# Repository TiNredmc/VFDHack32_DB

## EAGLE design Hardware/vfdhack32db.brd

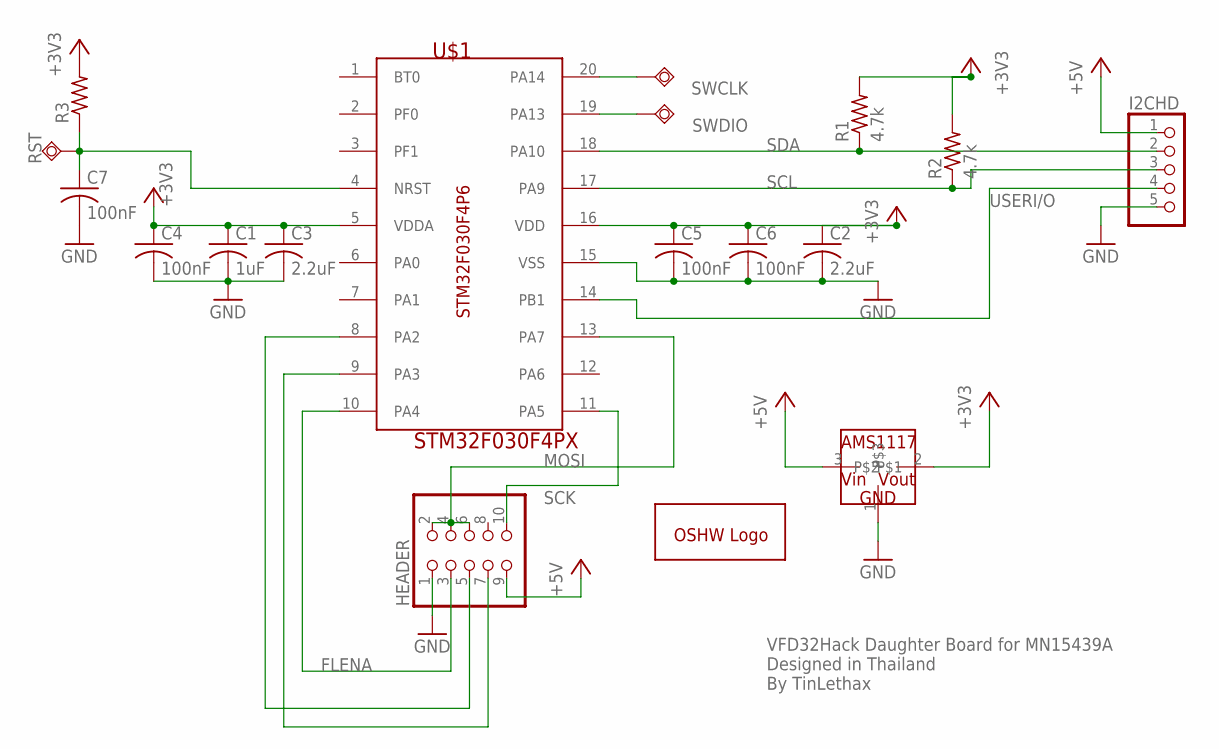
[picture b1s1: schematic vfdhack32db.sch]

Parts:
C1: 1uF; C0603
C2, C3: 2.2uF; C0603
C4, C5, C6, C7: 100nF; C1206K
GOLD_ORB_SM1: OSHWLOGOLOGO5MM; OSHW_5MM
HEADER: PINHD-2X5; 2X05
I2CHD: PINHD-1X5; 1X05
R1, R2: 4.7k; R0603
R3: R-US_R0603; R0603
RST: TPSQTP10SQ; TP10SQ
SWCLK: TPSQTP10SQ; TP10SQ
SWDIO: TPSQTP10SQ; TP10SQ
U$1: STM32F030F4PX; SOP65P640X120-20N
U$2: AMS1117; SOT223

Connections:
+3V3: C1.1, C2.1, C3.1, C4.1, C5.1, C6.1, R1.2, R2.2, R3.2, U$1.5 (VDDA), U$1.16 (VDD), U$2.2
+5V: HEADER.9, I2CHD.1, U$2.3
FLENA: HEADER.3, U$1.10 (PA4)
GND: C1.2, C2.2, C3.2, C4.2, C5.2, C6.2, C7.2, HEADER.1, I2CHD.5, U$1.15 (VSS), U$2.1
MOSI: HEADER.2, HEADER.4, HEADER.6, U$1.13 (PA7)
unnamed: C7.1, R3.1, RST.TP, U$1.4 (NRST)
unnamed: SWCLK.TP, U$1.20 (PA14)
unnamed: SWDIO.TP, U$1.19 (PA13)
unnamed: HEADER.5, U$1.8 (PA2)
unnamed: HEADER.7, U$1.9 (PA3)
SCK: HEADER.10, U$1.11 (PA5)
SCL: I2CHD.3, R2.1, U$1.17 (PA9)
SDA: I2CHD.2, R1.1, U$1.18 (PA10)
USERI/O: I2CHD.4, U$1.14 (PB1)

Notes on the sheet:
VFD32Hack Daughter Board for MN15439A Designed in Thailand By TinLethax

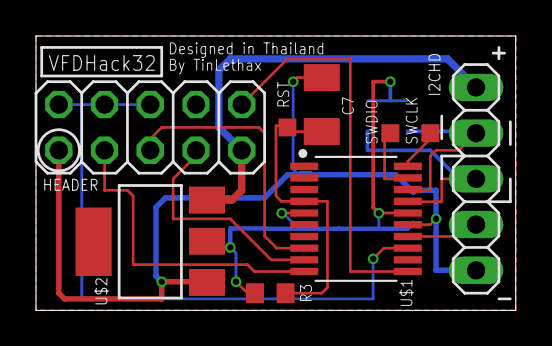
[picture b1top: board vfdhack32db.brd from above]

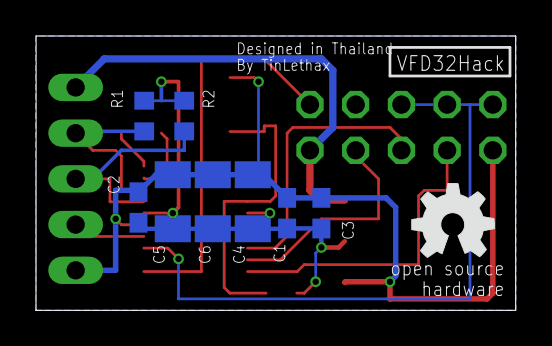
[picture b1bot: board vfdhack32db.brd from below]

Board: 2 copper layers, 26.6 x 15.2 mm, 18 parts (9 on the bottom side), 14 nets.

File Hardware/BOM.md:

# Bill of materials
1. x1 AMS1117 3v3   
2. x4 100nF 1206 capacitor 16v  
3. x2 2.2uF 0603 capacitor 16v   
4. x1 1uF 	0603 capacitor 16v  
5. x1 1x5 Male Pin header  
6. x1 2x5 Female Pin header or x2 1x5 Female Pin header 
7. x2 4.7k 0603  resistor
8. [OPTIONAL] x1 10k 0603 resistor for NRST pull up (internal pull up is there)  
9. x1 STM32F030F4P6 (TSSOP 20).

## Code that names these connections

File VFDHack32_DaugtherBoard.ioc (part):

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Mcu.Name=STM32F030F4Px
Mcu.Package=TSSOP20
Mcu.UserName=STM32F030F4Px
PA10.Mode=I2C
PA10.Signal=I2C1_SDA
PA13.Mode=Serial_Wire
PA13.Signal=SYS_SWDIO
PA14.Mode=Serial_Wire
PA14.Signal=SYS_SWCLK
PA2.GPIOParameters=GPIO_Speed,GPIO_Label
PA2.GPIO_Label=BLANK
PA2.GPIO_Speed=GPIO_SPEED_FREQ_HIGH
PA2.Signal=GPIO_Output
PA3.GPIOParameters=GPIO_Speed,GPIO_Label
PA3.GPIO_Label=LAT
PA3.GPIO_Speed=GPIO_SPEED_FREQ_HIGH
PA3.Signal=GPIO_Output
PA5.Mode=TX_Only_Simplex_Unidirect_Master
PA5.Signal=SPI1_SCK
PA7.Mode=TX_Only_Simplex_Unidirect_Master
PA7.Signal=SPI1_MOSI
PA9.Mode=I2C
PA9.Signal=I2C1_SCL
RCC.SYSCLKFreq_VALUE=48000000
RCC.SYSCLKSource=RCC_SYSCLKSOURCE_PLLCLK
board=custom

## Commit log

2021-08-25 Added file to repo
2021-08-25 - Added hardware files and BOMs. - corrected typo in readme.
2021-08-25 Create LICENSE
